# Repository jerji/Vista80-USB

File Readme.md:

This is the code and PCB for my old Vista80 keyboard usb converter board.
see: https://ingeniumcanada.org/ingenium/collection-research/collection-item.php?id=1992.0451.009

I will probably make a writeup soon.

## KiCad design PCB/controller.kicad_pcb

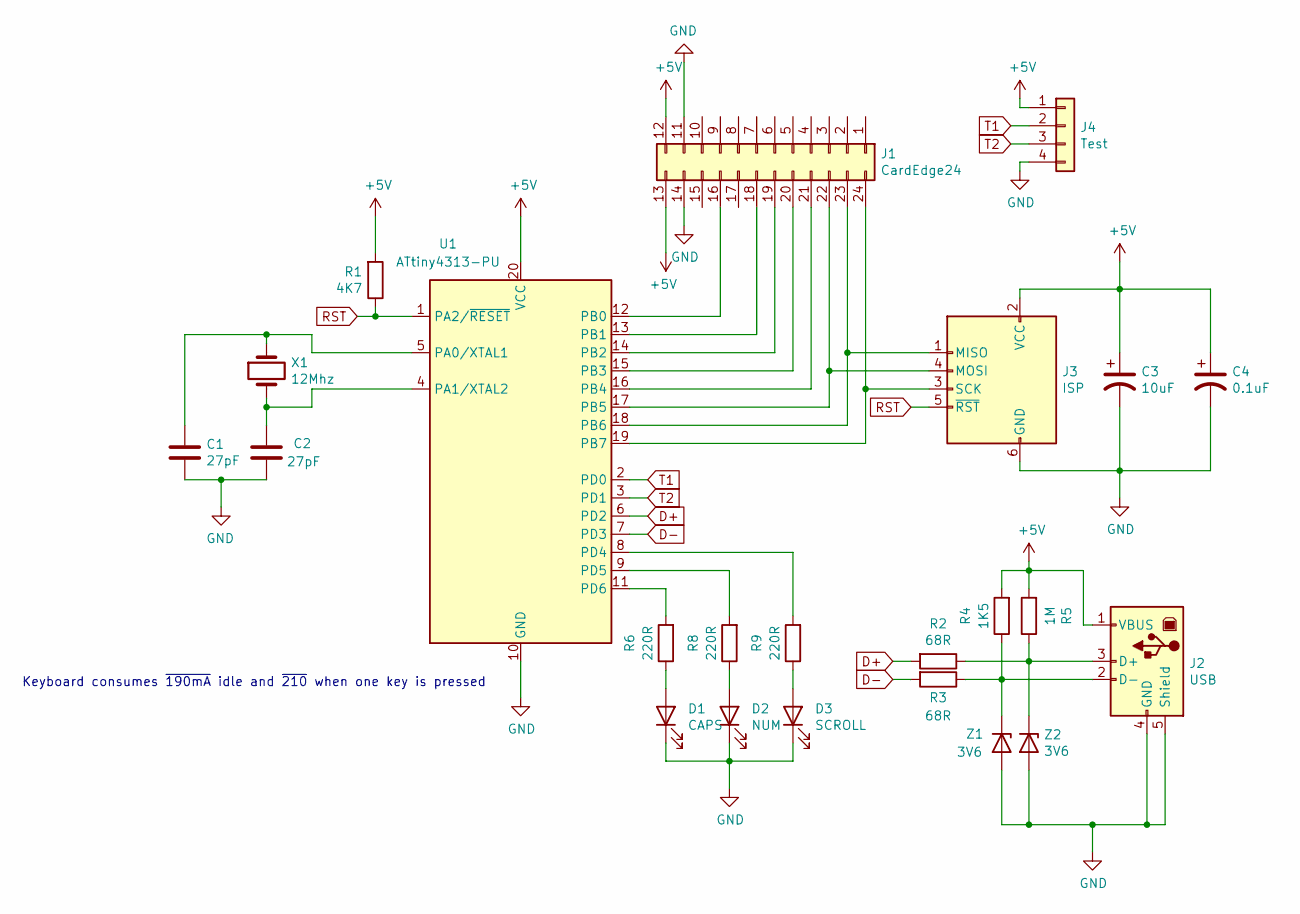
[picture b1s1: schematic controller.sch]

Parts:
C1, C2: 27pF; C_Disc_D7.5mm_W2.5mm_P5.00mm
C3: 10uF; CP_Radial_D4.0mm_P2.00mm
C4: 0.1uF; CP_Radial_D4.0mm_P2.00mm
D1: CAPS; LED_D3.0mm
D2: NUM; LED_D3.0mm
D3: SCROLL; LED_D3.0mm
J1: CardEdge24; DIP-24_200
J2: USB; USB_B_OST_USB-B1HSxx_Horizontal
J3: ISP; PinHeader_2x03_P2.54mm_Vertical
J4: Test; PinHeader_1x04_P2.54mm_Vertical
R1: 4K7; R_Axial_DIN0411_L9.9mm_D3.6mm_P12.70mm_Horizontal
R2, R3: 68R; R_Axial_DIN0411_L9.9mm_D3.6mm_P12.70mm_Horizontal
R4: 1K5; R_Axial_DIN0411_L9.9mm_D3.6mm_P12.70mm_Horizontal
R5: 1M; R_Axial_DIN0411_L9.9mm_D3.6mm_P12.70mm_Horizontal
R6, R8, R9: 220R; R_Axial_DIN0411_L9.9mm_D3.6mm_P12.70mm_Horizontal
U1: ATtiny4313-PU; DIP-20_W7.62mm
X1: 12Mhz; Crystal_HC18-U_Vertical
Z1, Z2: 3V6; D_5W_P12.70mm_Horizontal

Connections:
+5V: C3.1, C4.1, J1.12, J1.13, J2.1 (VBUS), J3.2 (VCC), J4.1, R1.2, R4.2, R5.2, U1.20 (VCC)
D+: R2.2, U1.6 (PD2)
D-: R3.2, U1.7 (PD3)
GND: C1.2, C2.2, C3.2, C4.2, D1.1 (K), D2.1 (K), D3.1 (K), J1.11, J1.14, J2.4 (GND), J2.5 (Shield), J3.6 (GND), J4.4, U1.10 (GND), Z1.2 (A), Z2.2 (A)
unnamed: C1.1, U1.5 (PA0/XTAL1), X1.1
unnamed: C2.1, U1.4 (PA1/XTAL2), X1.2
unnamed: D1.2 (A), R6.1
unnamed: D2.2 (A), R8.1
unnamed: D3.2 (A), R9.1
unnamed: J1.16, U1.12 (PB0)
unnamed: J1.18, U1.13 (PB1)
unnamed: J1.19, U1.14 (PB2)
unnamed: J1.20, U1.15 (PB3)
unnamed: J1.21, U1.16 (PB4)
unnamed: J1.22, J3.4 (MOSI), U1.17 (PB5)
unnamed: J1.23, J3.1 (MISO), U1.18 (PB6)
unnamed: J1.24, J3.3 (SCK), U1.19 (PB7)
unnamed: J2.2 (D-), R3.1, R4.1, Z1.1 (K)
unnamed: J2.3 (D+), R2.1, R5.1, Z2.1 (K)
unnamed: R6.2, U1.11 (PD6)
unnamed: R8.2, U1.9 (PD5)
unnamed: R9.2, U1.8 (PD4)
RST: J3.5 (~RST), R1.1, U1.1 (PA2/~RESET)
T1: J4.2, U1.2 (PD0)
T2: J4.3, U1.3 (PD1)

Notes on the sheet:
Keyboard consumes ~190mA idle and ~210 when one key is pressed

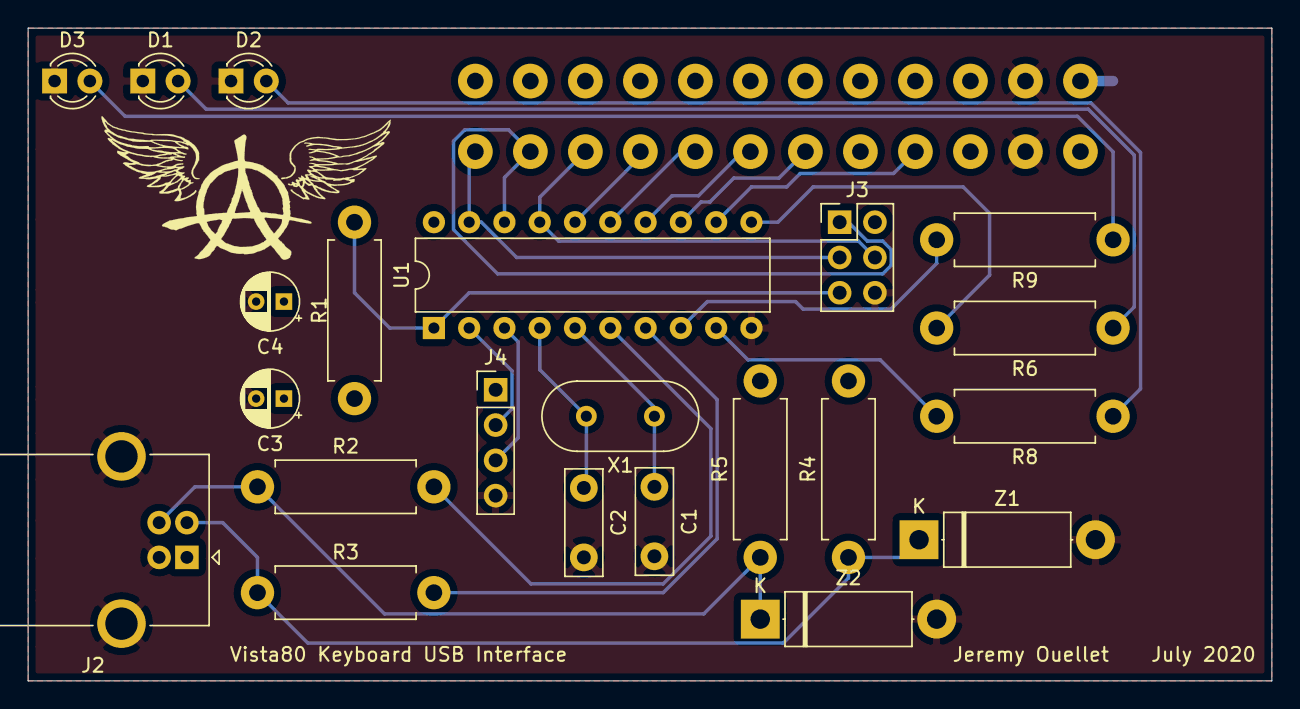
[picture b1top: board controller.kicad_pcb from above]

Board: 2 copper layers, 89.5 x 47.0 mm, 23 parts (1 on the bottom side), 25 nets.

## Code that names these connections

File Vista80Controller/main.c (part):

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	int sendCounter = 0;
	/*
	 Pin descriptions
	 PB0..PB7 Keyboard Matrix
	 PD0 Test Point 1
	 PD1 Test Point 2
	 PD2 D+
	 PD3 D-
	 PD4 Scroll Lock LED
	 PD5 Num Lock LED
	 PD6 Caps Lock LED
	 */

	hardwareInit();
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
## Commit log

2020-11-30 Litterally all the code
2020-11-30 Create gitignore
2020-11-30 gitIgnore actually
